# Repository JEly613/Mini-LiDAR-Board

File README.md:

# Mini-LiDAR-Board

This project fuses data from LiDAR and IMU measurements to reconstruct internal scans of a room. The LiDAR module is mounted on a custom 4-layer PCB that hosts an STM32 microcontroller and an ICM-42688-P IMU. The data from both sensors is collected by the microcontroller and sent via a custom USB protocol to the host software, where the room is reconstructed.

---

## Operation Principle

The board spins a LiDAR module that measures distances in a 2D plane. On its own that only ever produces a flat ring. The on-board IMU tracks how the boardis oriented, so every distance reading can be rotated out of the sensor's 2D plane and into a 3D environment. Tilting the sensor so that all 360 degrees of freedom are covered constructs a full scan of the room.

---

## Hardware

Designed using KiCad.

| | |
|---|---|
| **Board** | 4-layer, 82 × 82 mm, 49 components, 212 vias |
| **Stackup** | `F.Cu` signal · `In1.Cu` GND plane · `In2.Cu` VDD plane · `B.Cu` signal |
| **MCU** | STM32F411CEU6 — QFN-48, 7 × 7 mm, 0.5 mm pitch, 96 MHz |
| **IMU** | TDK ICM-42688-P — LGA-14, 2.5 × 3 mm, on SPI1 |
| **LiDAR** | Slamtec RPLIDAR A1, PWM-driven spindle |
| **Power** | USB-C in, AP2112K-3.3 LDO, 5 V and 3.3 V rails |
| **Clock** | 8 MHz ABM3B crystal → 96 MHz core + exact 48 MHz USB |

A few notable design decisions:

- **The IMU is mounted on the bottom copper**, rotated −90 degrees. I was worried about the brushed motor on the LiDAR creating noise that would interfere with the IMU, so I shielded it with a few layers of copper. I probably didn't need to but wanted to be safe.
- **The LiDAR motor supply is permanently on** through ferrite bead FB2, with no enable pin. The motor is only driven by the PWM signal, which sometimes causes issues with startup. Next revision I'll add a motor enable.
- **PA9 carries the LiDAR UART**, which means that the MCU can only be flashed through the SWD header.

Gerbers are in:
[`production/`](production/).

---

## Firmware

NOTE: Designed, tested, and validated by me. Implemented with the help of Claude Code.

Register-level bare-metal C with a **12 KB flash image**.

- 96 MHz core from the 8 MHz crystal, with the exact 48 MHz PLLQ that USB needs
- ICM-42688-P at 1 kHz over SPI1 with DMA, triggered by its data-ready interrupt
- 6-DOF Madgwick fusion at the full sample rate, with startup gyro-bias calibration
- RPLIDAR A1 `SCAN` decoding off USART1 with circular DMA and byte-level resync
- TIM2_CH3 PWM spindle control
- CRC-16 framed binary protocol, hardware watchdog, and independent stall
  detection for the IMU, the LiDAR link, and the spindle

Full detail in [`firmware/README.md`](firmware/README.md),
[`firmware/HARDWARE.md`](firmware/HARDWARE.md), and the wire format in
[`firmware/PROTOCOL.md`](firmware/PROTOCOL.md).

### Build and flash

Requires `arm-none-eabi-gcc` and `st-flash` (from stlink-tools).

```bash
cd firmware
make            # builds build/lidar-imu.bin and prints section sizes
make flash      # writes it over SWD
```

---

## Host software

NOTE: Designed, tested, and validated by me. Implemented with the help of Claude Code.

Python 3 with NumPy and matplotlib. Reads the USB CDC stream, parses the binary
protocol, and renders three views.

```bash
cd host
python3 -m pip install -r requirements.txt

python3 -m lidarscan              # live orientation + LiDAR rings
python3 -m lidarscan --cloud      # 3D point cloud, device fixed at the origin
python3 -m lidarscan --cloud-ins  # 3D point cloud with dead-reckoned position
python3 -m lidarscan --sim        # synthetic data, no hardware needed
python3 -m lidarscan --selftest   # 60 self-tests covering the transform chain
```

`--cloud` assumes the device only rotates in place. `--cloud-ins` additionally
double-integrates the accelerometer to estimate translation — see
[`host/lidarscan/cloud_ins.py`](host/lidarscan/cloud_ins.py) for the error budget
and why it drifts. Both write binary PLY that opens in MeshLab, CloudCompare, or
Blender.

### Coordinate frames

Getting these straight is most of the work:

| Frame | Definition |
|---|---|
| **Sensor** | Raw ICM-42688-P axes. What the Madgwick filter integrates. |
| **Body** | The board: X forward, Y left, Z up. `+Y` sensor is forward, `−Z` sensor is up. |
| **Earth** | Madgwick's output frame, Z up. Yaw has no absolute reference. |
| **LiDAR** | The A1's scan plane, related to the body frame by its physical mounting. |

The A1 is a separate module on a cable, so its orientation relative to the PCB
is mechanical and cannot be known from code. `--lidar-yaw-deg` aligns forward and
`--lidar-ccw` un-mirrors the sweep; set them once for your mounting.

---

## Repository layout

```
firmware/          bare-metal STM32F411 firmware
  src/             16 C source files
  include/         headers, incl. board.h — the authoritative pin map
  cmsis/           vendored ARM CMSIS headers
  PROTOCOL.md      normative wire format
  HARDWARE.md      pin map, DMA allocation, link budget
host/
  lidarscan/       Python host application
    protocol.py    framing, CRC, packet encode/decode
    reader.py      serial + simulated sources
    viz.py         orientation and ring views
    cloud.py       3D reconstruction, rotation only
    cloud_ins.py   3D reconstruction with dead reckoning
production/        gerbers, drill, pick-and-place
docs/images/       photos and screenshots for this README
*.kicad_*          schematic and PCB source
```

---

## Status and known limitations

Working end to end: the board is fabricated, assembled, and validated driving
the IMU, LiDAR, and USB concurrently at 0.00% measured packet loss and 5.6 rev/s
sustained scanning.

Known limits, all understood rather than mysterious:

- **Yaw drifts.** A 6-DOF filter has no magnetic reference, so long sessions
  smear the cloud about the vertical axis. Sweep and look; don't leave it
  accumulating for ten minutes and expect crisp walls.
- **`--cloud-ins` position drifts as t².** Double integration of a MEMS
  accelerometer diverges; zero-velocity updates and bias tracking bound it but
  cannot repeal it. Pause frequently while scanning.
- **Orientation packets are decimated 10:1 without an anti-alias filter**, so
  vibration above 50 Hz aliases into the band the dead-reckoner integrates.
  Averaging the samples in firmware would fix it.
- **The −90° IMU mounting rotation is not separately calibrated** — only the
  Z-flip is handled, via the stated sensor-to-body convention.

---

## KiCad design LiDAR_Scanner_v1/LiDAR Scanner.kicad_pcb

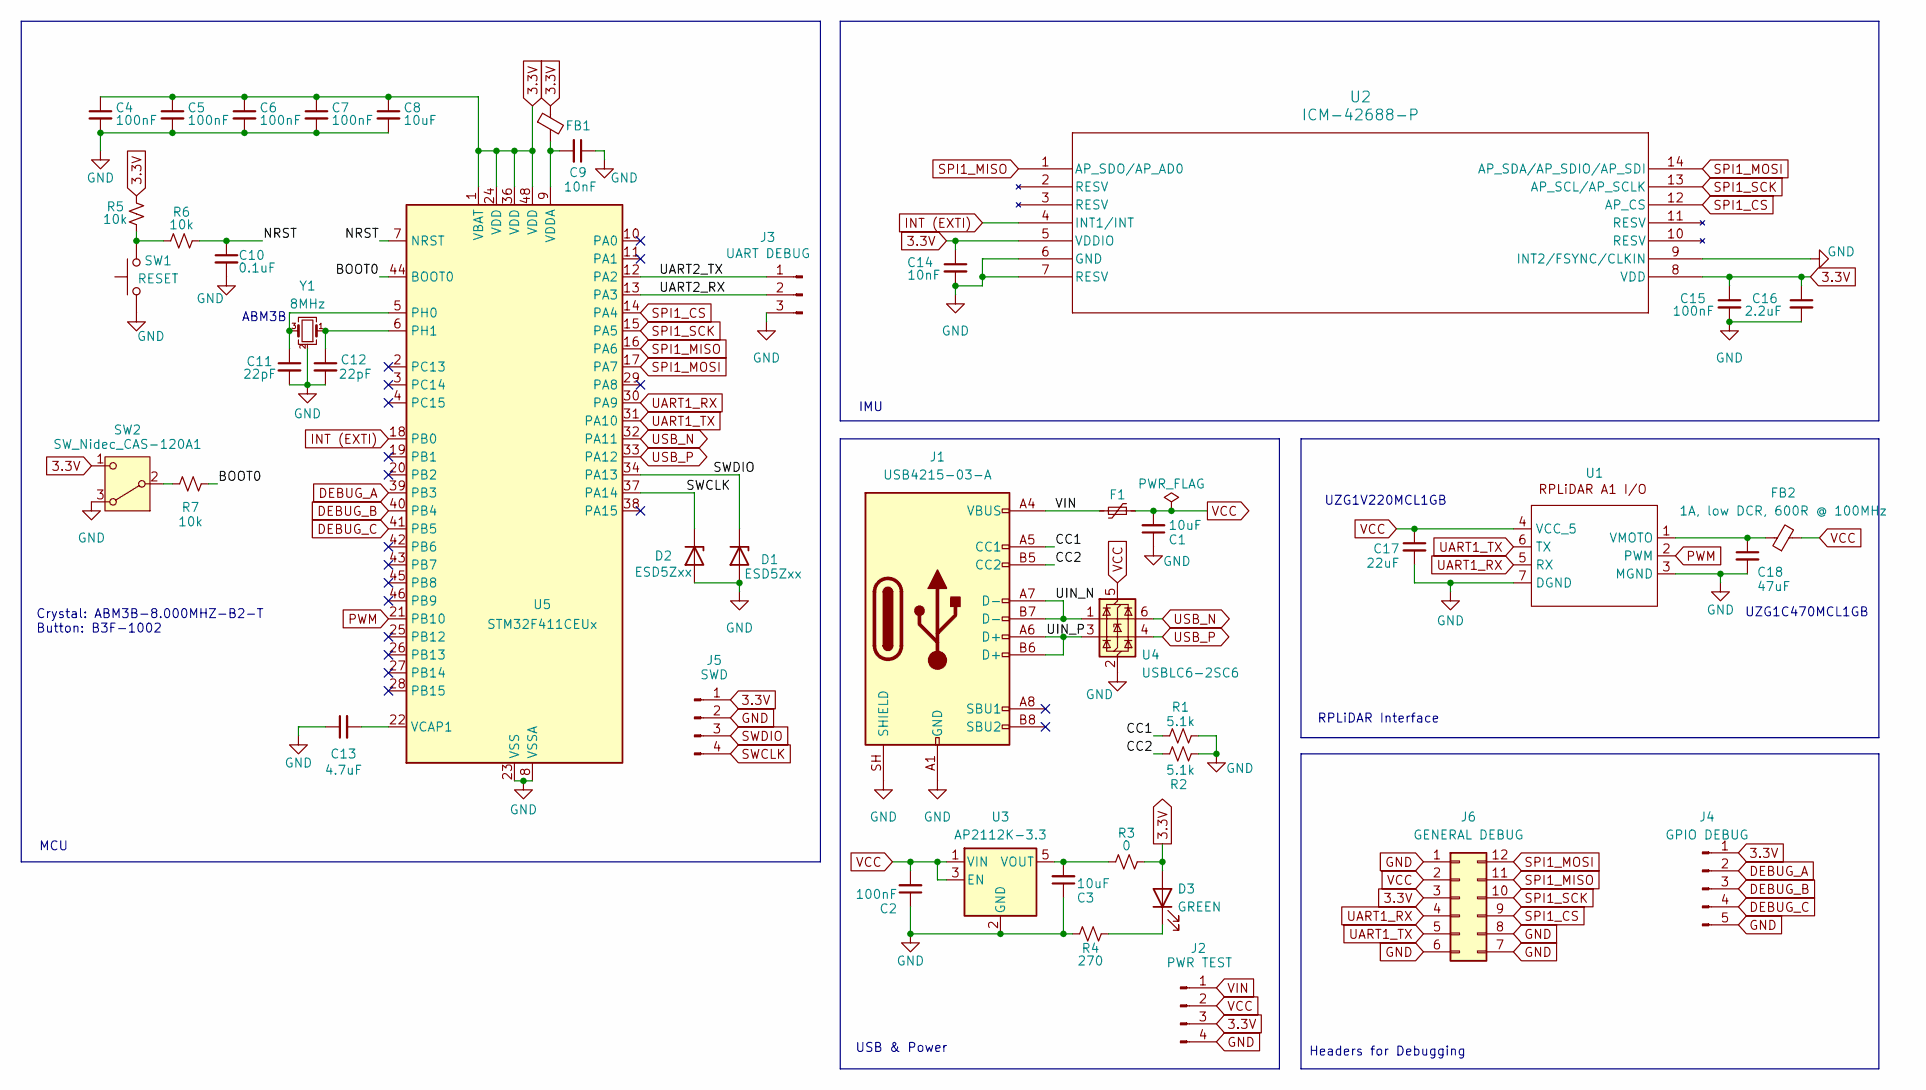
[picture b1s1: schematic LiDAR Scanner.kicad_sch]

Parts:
C1, C3, C8: 10uF; C_0603_1608Metric_Pad1.08x0.95mm_HandSolder
C2, C4, C5, C6, C7, C15: 100nF; C_0603_1608Metric_Pad1.08x0.95mm_HandSolder
C9, C14: 10nF; C_0603_1608Metric_Pad1.08x0.95mm_HandSolder
C10: 0.1uF; C_0603_1608Metric_Pad1.08x0.95mm_HandSolder
C11, C12: 22pF; C_0603_1608Metric_Pad1.08x0.95mm_HandSolder
C13: 4.7uF; C_0603_1608Metric_Pad1.08x0.95mm_HandSolder
C16: 2.2uF; C_0603_1608Metric_Pad1.08x0.95mm_HandSolder
C17: 22uF; PCAP_6.3x3-ELECT_NCA-L
C18: 47uF; PCAP_6.3x3-ELECT_NCA-L
D1, D2: ESD5Zxx; D_SOD-523
D3: GREEN; LED_0805_2012Metric_Pad1.15x1.40mm_HandSolder
F1: Polyfuse_Small; Fuse_0805_2012Metric_Pad1.15x1.40mm_HandSolder
FB1: FerriteBead_Small; L_0603_1608Metric_Pad1.05x0.95mm_HandSolder
FB2: 1A, low DCR, 600R @ 100MHz; L_0805_2012Metric_Pad1.05x1.20mm_HandSolder
J1: USB4215-03-A; GCT_USB4215-03-A_REVA
J2: PWR TEST; PinHeader_1x04_P2.54mm_Vertical
J3: UART DEBUG; PinHeader_1x03_P2.54mm_Vertical
J4: GPIO DEBUG; PinHeader_1x05_P2.54mm_Vertical
J5: SWD; PinHeader_1x04_P2.54mm_Vertical
J6: GENERAL DEBUG; PinHeader_2x06_P2.54mm_Vertical
R1, R2: 5.1k; C_0603_1608Metric_Pad1.08x0.95mm_HandSolder
R3: 0; C_0603_1608Metric_Pad1.08x0.95mm_HandSolder
R4: 270; C_0603_1608Metric_Pad1.08x0.95mm_HandSolder
R5, R6: 10k; C_0603_1608Metric_Pad1.08x0.95mm_HandSolder
R7: 10k; R_0603_1608Metric_Pad0.98x0.95mm_HandSolder
SW1: RESET; SW_B3F-1000_OMR
SW2: SW_Nidec_CAS-120A1; Nidec_Copal_CAS-120A
U1: CONN_22035075_MOL
U2: ICM-42688-P; LGA14_2P5X3X0P91_TDK
U3: AP2112K-3.3; SOT-23-5
U4: USBLC6-2SC6; SOT-23-6
U5: STM32F411CEUx; QFN-48-1EP_7x7mm_P0.5mm_EP5.6x5.6mm
Y1: 8MHz; ABM3B_ABR

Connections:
3.3V: C4.1, C5.1, C6.1, C7.1, C8.1, C14.1, C15.1, C16.1, D3.2 (A), FB1.1, J2.3, J4.1, J5.1, J6.3, R3.2, R5.1, SW2.1 (C), U2.5 (VDDIO), U2.8 (VDD), U5.1 (VBAT), U5.24 (VDD), U5.36 (VDD), U5.48 (VDD)
/BOOT0: R7.2, U5.44 (BOOT0)
/CC1: J1.A5 (CC1), R1.2
/CC2: J1.B5 (CC2), R2.2
/NRST: C10.1, R6.2, U5.7 (NRST)
/UART2_RX: J3.2, U5.13 (PA3)
/UART2_TX: J3.1, U5.12 (PA2)
/UIN_N: J1.A7 (D-), J1.B7 (D-), U4.1 (I/O1)
/UIN_P: J1.A6 (D+), J1.B6 (D+), U4.3 (I/O2)
DEBUG_A: J4.2, U5.39 (PB3)
DEBUG_B: J4.3, U5.40 (PB4)
DEBUG_C: J4.4, U5.41 (PB5)
GND: C1.1, C2.1, C3.1, C4.2, C5.2, C6.2, C7.2, C8.2, C9.1, C10.2, C11.2, C12.2, C13.1, C14.2, C15.2, C16.2, C17.2, C18.2, D1.2 (A), D2.2 (A), J1.A1 (GND), J1.A12 (GND), J1.B1 (GND), J1.B12 (GND), J1.SH (SHIELD), J2.4, J3.3, J4.5, J5.2, J6.1, J6.6, J6.7, J6.8, R1.1, R2.1, R4.1, SW1.1, SW2.3 (A), U1.3 (MGND), U1.7 (DGND), U2.6 (GND), U2.7 (RESV), U2.9 (INT2/FSYNC/CLKIN), U3.2 (GND), U4.2 (GND), U5.8 (VSSA), U5.23 (VSS), U5.35 (VSS), U5.47 (VSS), U5.49 (VSS), Y1.2 (G), Y1.4 (G)
INT (EXTI): U2.4 (INT1/INT), U5.18 (PB0)
unnamed: D3.1 (K), R4.2
unnamed: R5.2, R6.1, SW1.2
unnamed: R7.1, SW2.2 (B)
unnamed: C18.1, FB2.1, U1.1 (VMOTO)
unnamed: C3.2, R3.1, U3.5 (VOUT)
unnamed: C11.1, U5.5 (PH0), Y1.3
unnamed: C12.1, U5.6 (PH1), Y1.1
unnamed: C13.2, U5.22 (VCAP1)
unnamed: C9.2, FB1.2, U5.9 (VDDA)
PWM: U1.2 (PWM), U5.21 (PB10)
SPI1_CS: J6.9, U2.12 (AP_CS), U5.14 (PA4)
SPI1_MISO: J6.11, U2.1 (AP_SDO/AP_AD0), U5.16 (PA6)
SPI1_MOSI: J6.12, U2.14 (AP_SDA/AP_SDIO/AP_SDI), U5.17 (PA7)
SPI1_SCK: J6.10, U2.13 (AP_SCL/AP_SCLK), U5.15 (PA5)
SWCLK: D2.1 (K), J5.4, U5.37 (PA14)
SWDIO: D1.1 (K), J5.3, U5.34 (PA13)
UART1_RX: J6.4, U1.5 (RX), U5.30 (PA9)
UART1_TX: J6.5, U1.6 (TX), U5.31 (PA10)
USB_N: U4.6 (I/O1), U5.32 (PA11)
USB_P: U4.4 (I/O2), U5.33 (PA12)
VCC: C1.2, C2.2, C17.1, F1.2, FB2.2, J2.2, J6.2, U1.4 (VCC_5), U3.1 (VIN), U3.3 (EN), U4.5 (VBUS)
VIN: F1.1, J1.A4 (VBUS), J1.A9 (VBUS), J1.B4 (VBUS), J1.B9 (VBUS), J2.1

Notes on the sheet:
MCU
UZG1V220MCL1GB
RPLiDAR Interface
USB & Power
UZG1C470MCL1GB
Headers for Debugging
ABM3B
IMU
Crystal: ABM3B-8.000MHZ-B2-T Button: B3F-1002

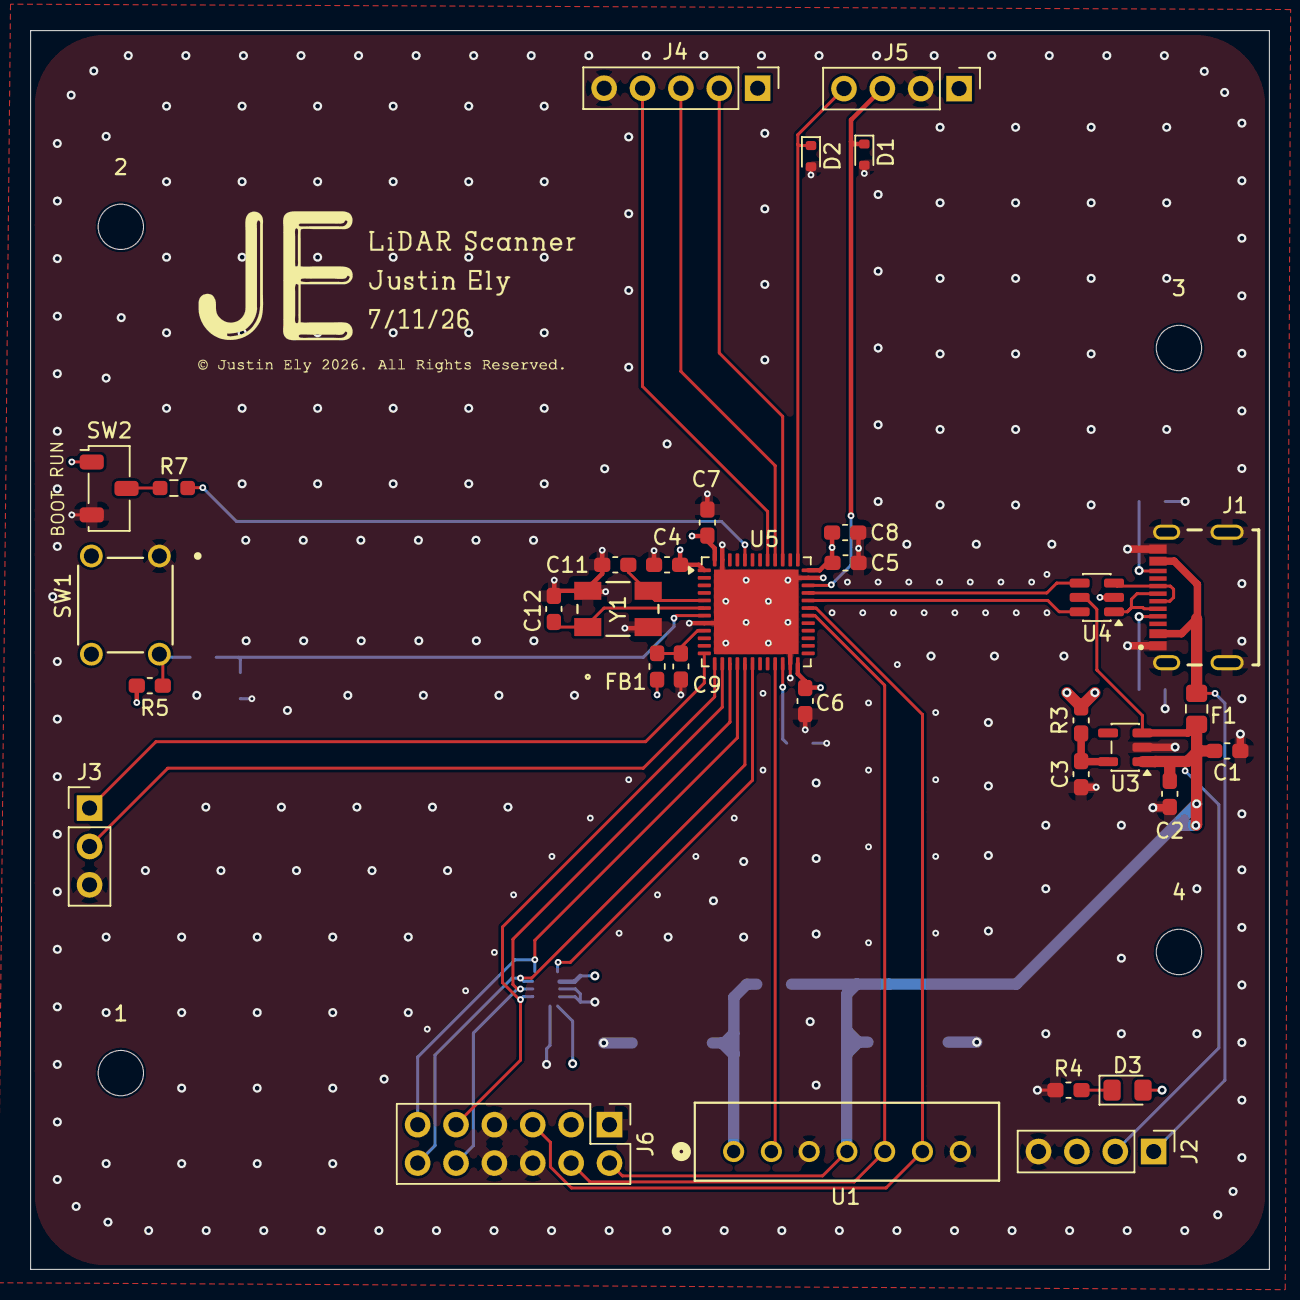
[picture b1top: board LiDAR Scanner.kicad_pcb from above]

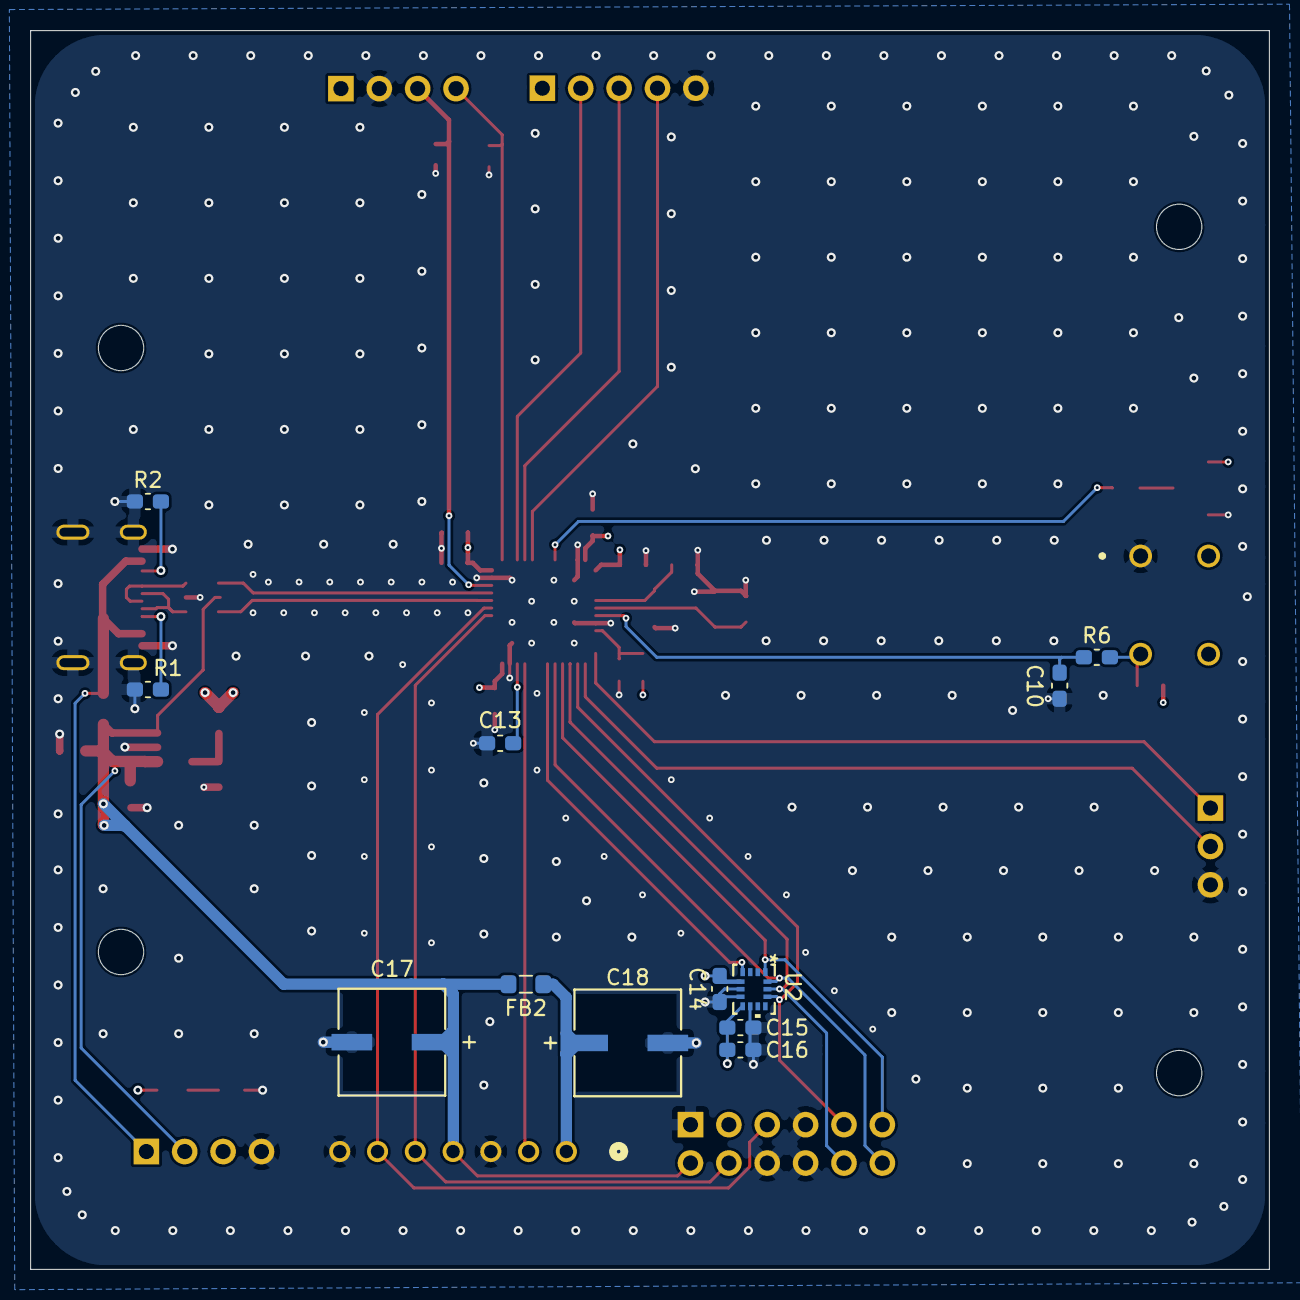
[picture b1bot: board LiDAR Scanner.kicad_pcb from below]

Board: 4 copper layers, 82.0 x 82.0 mm, 49 parts (12 on the bottom side), 36 nets.

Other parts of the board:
1, 2, 3, 4: MountingHole_3mm

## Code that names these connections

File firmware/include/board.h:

/* ---------------------------------------------------------------------------
 * board.h -- Mini-LiDAR-Board hardware description.
 *
 * Every pin assignment in this file was read out of the project's KiCad
 * netlist ("LiDAR Scanner.kicad_sch" / ".kicad_pcb"), not out of the project
 * write-up.  Where the two disagree, the KiCad files win.  See HARDWARE.md for
 * the list of places where the older project guide is wrong.
 *
 * MCU : STM32F411CEU6, UFQFPN-48, 512 KiB flash / 128 KiB SRAM
 * XTAL: 8 MHz HSE on PH0/PH1 (Y1, 22 pF load caps).  There is NO 32.768 kHz
 *       LSE crystal on this board.
 * ------------------------------------------------------------------------- */

#ifndef BOARD_H
#define BOARD_H

#include "stm32f411xe.h"

/* ---------------------------------------------------------------------------
 * Clock tree (see clock.c for the derivation and the RM0383 constraints)
 * ------------------------------------------------------------------------- */
#define BOARD_HSE_HZ      8000000UL   /* Y1                                    */
#define BOARD_SYSCLK_HZ   96000000UL  /* PLL P output                          */
#define BOARD_AHB_HZ      96000000UL  /* AHB prescaler /1                      */
#define BOARD_APB1_HZ     48000000UL  /* APB1 /2  -- must stay <= 50 MHz       */
#define BOARD_APB2_HZ     96000000UL  /* APB2 /1  -- limit is 100 MHz          */
#define BOARD_APB1_TIM_HZ 96000000UL  /* APB1 timers run at 2x PCLK1 (/2 pre)  */
#define BOARD_USB48_HZ    48000000UL  /* PLL Q output, exact 48 MHz for OTG_FS */

/* ---------------------------------------------------------------------------
 * IMU: U2, InvenSense/TDK ICM-42688-P, LGA-14, SPI only.
 *
 *   VDD and VDDIO are both on the 3.3 V rail.
 *   Pin 9 (INT2/FSYNC/CLKIN) is HARD-TIED TO GND on this board, so INT2 and
 *   FSYNC are unavailable -- INT1 on PB0 is the only interrupt path.  The
 *   driver must therefore never configure INT2 as a push-pull output.
 * ------------------------------------------------------------------------- */
#define IMU_CS_PORT     GPIOA
#define IMU_CS_PIN      4U            /* PA4, software-driven chip select      */
#define IMU_SCK_PIN     5U            /* PA5, SPI1_SCK,  AF5                   */
#define IMU_MISO_PIN    6U            /* PA6, SPI1_MISO, AF5                   */
#define IMU_MOSI_PIN    7U            /* PA7, SPI1_MOSI, AF5                   */
#define IMU_INT_PORT    GPIOB
#define IMU_INT_PIN     0U            /* PB0, ICM-42688-P INT1 -> EXTI0        */

/* ---------------------------------------------------------------------------
 * USB: USB-C connector on the OTG_FS full-speed PHY.
 *
 *   PA9 (the OTG_FS VBUS sense pin) is wired to the LiDAR UART instead, so
 *   VBUS sensing MUST be disabled in GCCFG (NOVBUSSENS = 1).  See usb_cdc.c.
 * ------------------------------------------------------------------------- */
#define USB_DM_PIN      11U           /* PA11, USB_OTG_FS_DM, AF10             */
#define USB_DP_PIN      12U           /* PA12, USB_OTG_FS_DP, AF10             */

/* ---------------------------------------------------------------------------
 * Debug UART: header J3 (1 = TX, 2 = RX, 3 = GND), USART2, 921600 8N1.
 *
 * NOT IMPLEMENTED IN THIS MILESTONE.  These defines record the wiring only --
 * no USART2 driver exists yet, and the firmware leaves PA2/PA3 in their reset
 * state.  All telemetry and status reporting goes over USB CDC instead.  Kept
 * here so a printf-style side channel can be added without re-reading the
 * netlist.
 * ------------------------------------------------------------------------- */
#define DBGUART_TX_PIN  2U            /* PA2, USART2_TX, AF7                   */
#define DBGUART_RX_PIN  3U            /* PA3, USART2_RX, AF7                   */
#define DBGUART_BAUD    921600UL

/* ---------------------------------------------------------------------------
 * Scope/logic-analyser header J4.  These are the ONLY visual indicators this
 * board has -- there are NO GPIO status LEDs (D3 is a bare power LED wired
 * across 3V3 through R4, with no MCU connection at all).
 * ------------------------------------------------------------------------- */
#define DEBUG_PORT      GPIOB
#define DEBUG_A_PIN     3U            /* PB3 -- toggled on each IMU sample     */
#define DEBUG_B_PIN     4U            /* PB4 -- toggled on each Madgwick step  */
#define DEBUG_C_PIN     5U            /* PB5 -- toggled on each packet TX      */

/* ---------------------------------------------------------------------------
 * SWD programming header J5: 1 = 3V3, 2 = GND, 3 = SWDIO (PA13), 4 = SWCLK
 * (PA14).  Left in their reset state; the firmware never touches PA13/PA14.
 * ------------------------------------------------------------------------- */

/* ---------------------------------------------------------------------------
 * LiDAR: Slamtec RPLIDAR A1 on connector U1 (Molex 22035075).
 *
 * U1 pinout, from the netlist:
 *   1 VMOTO  -- 5 V through ferrite bead FB2, with 47 uF bulk (C18).
 *               The motor supply is PERMANENTLY ON; there is no enable GPIO
 *               and no solder jumper, so rotation speed is set ONLY by the
 *               PWM pin below.  Driving PWM to 0 % is the only way to stop
 *               the motor.
 *   2 PWM    -- PB10, TIM2_CH3, AF1.  Motor speed control.
 *   3 MGND   -- motor ground
 *   4 VCC_5  -- 5 V logic supply (through polyfuse F1)
 *   5 RX     -- the LiDAR's receive pin, driven by the MCU's USART1_TX (PA9)
 *   6 TX     -- the LiDAR's transmit pin, read by the MCU's USART1_RX (PA10)
 *   7 DGND   -- digital ground
 *
 * NOTE ON THE NET NAMES: the schematic nets are called UART1_RX and UART1_TX
 * from the LiDAR's point of view, so "UART1_RX" lands on the MCU's PA9, which
 * is USART1_TX.  The wiring is correct; only the labels are confusing.
 *
 * The link runs at 115200 baud.  At 5 bytes per sample that is a hard ceiling
 * of ~2300 samples/s, which at the A1's default ~5.5 rev/s gives ~360-400
 * points per revolution.
 * ------------------------------------------------------------------------- */
#define LIDAR_UART_TX_PIN   9U        /* PA9,  USART1_TX -> LiDAR RX, AF7     */
#define LIDAR_UART_RX_PIN   10U       /* PA10, USART1_RX <- LiDAR TX, AF7     */
#define LIDAR_UART_BAUD     115200UL

#define LIDAR_PWM_PORT      GPIOB
#define LIDAR_PWM_PIN       10U       /* PB10, TIM2_CH3, AF1                  */

/* ---------------------------------------------------------------------------
 * DMA assignments (RM0383 Table 28).  Written down in one place because the
 * two subsystems constrain each other:
 *
 *   SPI1_RX   : DMA2 Stream 0 ch 3   <- taken (spi1_dma.c)
 *   SPI1_TX   : DMA2 Stream 3 ch 3   <- taken (spi1_dma.c)
 *   USART1_RX : DMA2 Stream 5 ch 4   <- taken (usart1_dma.c)
 *
 * USART1_RX can only live on Stream 2 or Stream 5, and SPI1_RX can only live
 * on Stream 0 or Stream 2.  Putting SPI1 on Stream 0 kept both USART1 options
 * open; we take Stream 5 and leave Stream 2 spare.
 * ------------------------------------------------------------------------- */

/* Convenience: 96-bit factory unique device ID, used to build the USB serial
 * number string so several boards can be told apart on one host. */
#define BOARD_UID_BASE  0x1FFF7A10UL

#endif /* BOARD_H */

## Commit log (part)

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2026-06-16 using github for backup
2026-06-26 finished v1 schematic
